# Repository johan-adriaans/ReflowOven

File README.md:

# ReflowOven
Arduino reflow oven voor de BEEA avond, 6 augustus 2015

De "bill-of-materials" staat [hier](board-v1/bill-of-materials.pdf).

## Opbouw reflow printje

Dit zijn de verbindingen op het bordje dat je gaat opbouwen:

### Stap 1: alle lage componenten

Let op de polariteit van de 3 LEDs en de zener diode!

Het knopje is een andere dan oorspronkelijk op de print voorzien is.

### Stap 2: drie connectoren

DC jack, kleine sensor aansluiting, grote heater aansluting:

Goed vastsolderen, vooral die DC voeding jack.

### Stap 3: Arduino Nano microcontroller

Pennen afknippen, zodat de onderkant redelijk vlak is.

### Stap 4: zoemer en extra dikke condensator

Let op polariteit van beide componenten:

### Stap 5: sensor + heater

De sensor in de groene schroefklemmen, heater in de blauwe:

Draden blank maken, liefst strippen en vertinnen, dan goed vastschroeven.

### Stap 6: software

Er moet een Arduino "sketch" in de Arduino worden geinstalleerd.  
Dat gaat via de USB stekker, en een USB driver voor de CH341 chip.  
De groene LED is altijd aan als de interne 5V regelaar stroom krijgt.

**Niet** de 19V voeding aansluiten tijdens deze actie!

### Stap 7

Controleren, controleren, controleren. En dan: _nog een laatste keertje..._  
Als bijvoorbeeld de zener verkeerd om zit, krijg je gegarandeerd vuurwerk.  
Pas als je zeker weet dat de zaak klopt, de 19V adapter inprikken.

Als alles goed aangesloten en ingesteld is, begint het plaatje warm te worden.  
Zet de zaak **alleen** aan als de heater goed in het koelblok geklemd zit!

## Opbouw demo bordje

...

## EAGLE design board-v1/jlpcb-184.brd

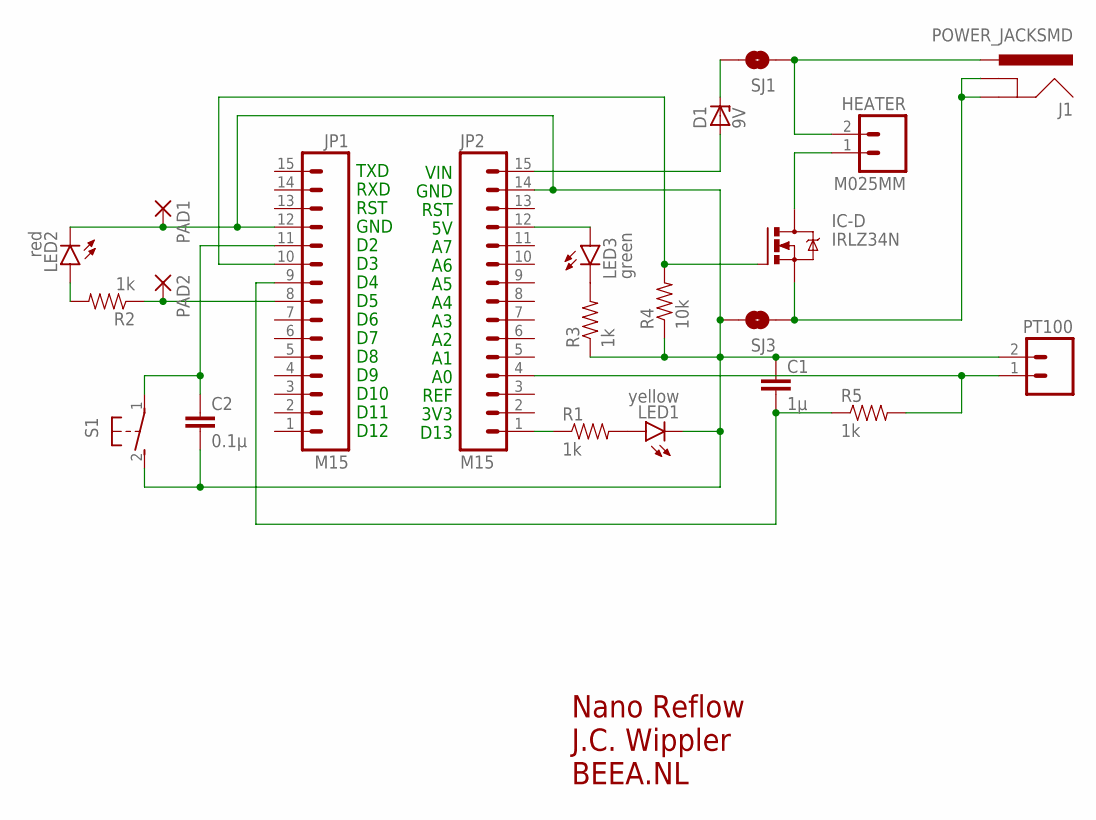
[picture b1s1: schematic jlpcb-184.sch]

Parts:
C1: 1µ; CAP-PTH-5MM
C2: 0.1µ; CAP-PTH-SMALL
D1: 9V; DO35Z10
HEATER: M025MM; SCREWTERMINAL-5MM-2
IC-D: IRLZ34N; TO220BV
J1: POWER_JACKSMD; POWER_JACK_SMD
JP1, JP2: M15; 1X15
LED1: yellow; LED3MM
LED2: red; LED3MM
LED3: green; LED3MM
PAD1, PAD2: 1,6/0,8
PT100: M023.5MM; SCREWTERMINAL-3.5MM-2
R1, R2, R3, R5: 1k; AXIAL-0.3
R4: 10k; AXIAL-0.3
S1: 31-XX; B3F-31XX
SJ1, SJ3: SOLDERJUMPERTRACE; SJ_2S-TRACE

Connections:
unnamed: D1.A, JP2.15
unnamed: D1.C, SJ1.2
unnamed: HEATER.1, IC-D.D
unnamed: IC-D.S, J1.GND (GNDBREAK), J1.P$4 (GND), SJ3.1
unnamed: C1.1, C2.2, JP1.12, JP2.14, LED1.K (C), LED2.K (C), PAD1.1, PT100.2, R3.P$1 (1), R4.P$1 (1), S1.2 (S), SJ3.2
unnamed: HEATER.2, J1.VIN0 (PWR), SJ1.1
unnamed: LED2.A, R2.P$2 (2)
unnamed: LED1.A, R1.P$2 (2)
unnamed: JP2.1, R1.P$1 (1)
unnamed: JP2.4, PT100.1, R5.P$2 (2)
unnamed: LED3.K (C), R3.P$2 (2)
unnamed: JP2.12, LED3.A
unnamed: IC-D.G, JP1.10, R4.P$2 (2)
unnamed: JP1.8, PAD2.1, R2.P$1 (1)
unnamed: C1.2, JP1.9, R5.P$1 (1)
unnamed: C2.1, JP1.11, S1.1

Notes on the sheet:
D12
D11
D10
GND
RST
RXD
TXD
D13
3V3
REF
VIN
Nano Reflow J.C. Wippler BEEA.NL

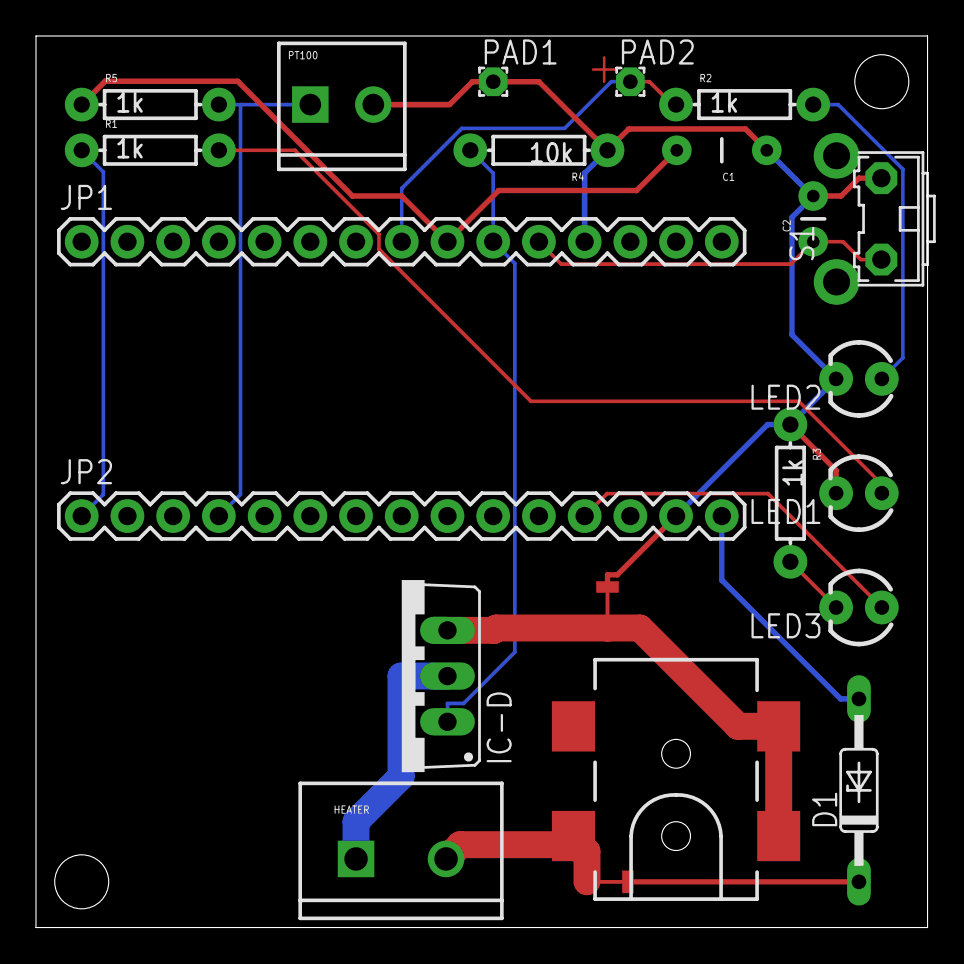
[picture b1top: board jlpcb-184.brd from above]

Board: 2 copper layers, 49.5 x 49.5 mm, 22 parts (0 on the bottom side), 16 nets.

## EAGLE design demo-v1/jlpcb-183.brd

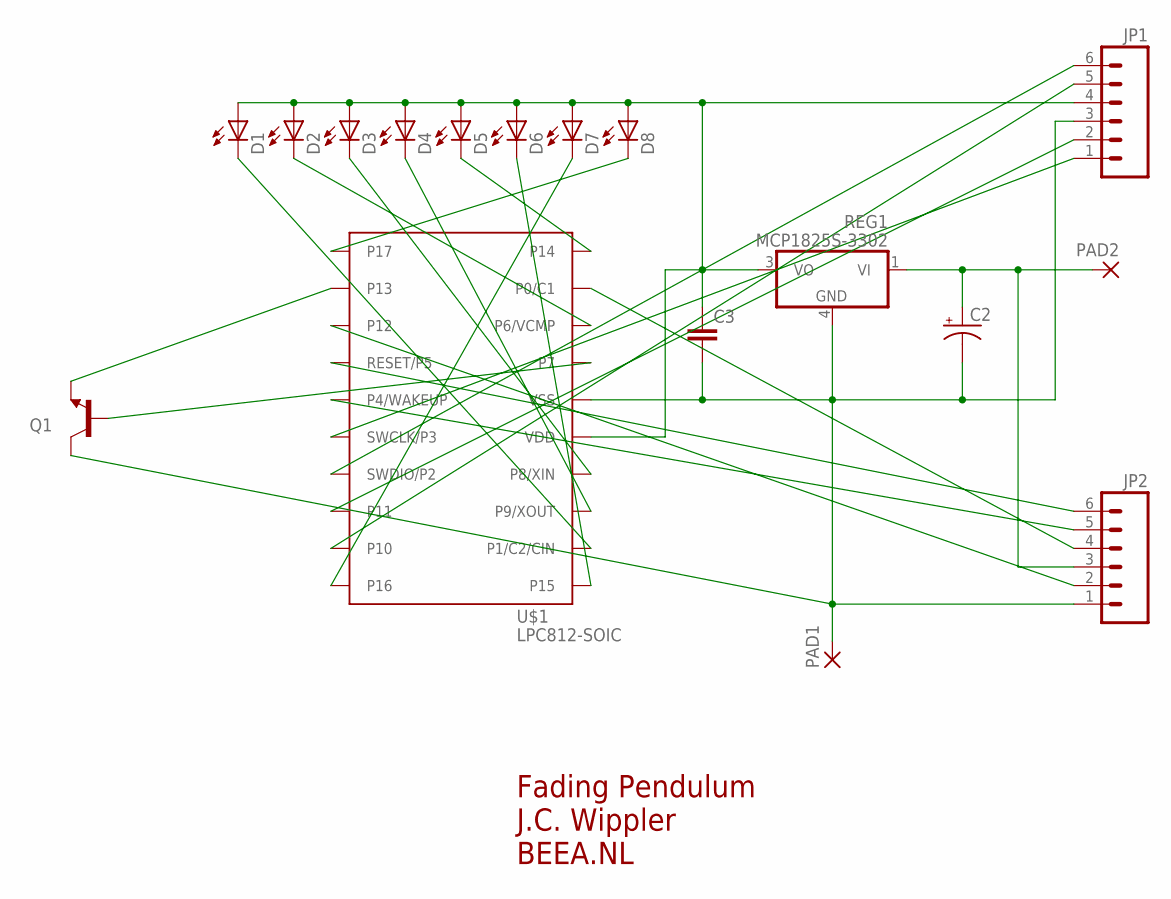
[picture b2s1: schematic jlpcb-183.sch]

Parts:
C2: CAP_POL1206; EIA3216
C3: CAP0805; 0805
D1, D2, D3, D4, D5, D6, D7, D8: LEDCHIP-LED0805; CHIP-LED0805
JP1, JP2: M06NO_SILK_FEMALE_PTH; 1X06_NO_SILK
PAD1, PAD2: SMD2; SMD1,27-2,54
Q1: TRANSISTOR_NPNSOT23-3; SOT23-3
REG1: MCP1825S-3302; SOT223
U$1: LPC812-SOIC; SOIC20

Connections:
unnamed: D1.C, U$1.12 (P1/C2/CIN)
unnamed: D2.C, U$1.18 (P6/VCMP)
unnamed: D3.C, U$1.14 (P8/XIN)
unnamed: D4.C, U$1.13 (P9/XOUT)
unnamed: D5.C, U$1.20 (P14)
unnamed: D6.C, U$1.11 (P15)
unnamed: D7.C, U$1.10 (P16)
unnamed: D8.C, U$1.1 (P17)
unnamed: C3.1, D1.A, D2.A, D3.A, D4.A, D5.A, D6.A, D7.A, D8.A, JP1.4, REG1.3 (VO), U$1.15 (VDD)
unnamed: C2.C (-), C3.2, JP1.3, JP2.1, PAD1.1, Q1.3 (C), REG1.4 (GND), U$1.16 (VSS)
unnamed: C2.A (+), JP2.3, PAD2.1, REG1.1 (VI)
unnamed: JP2.2, U$1.3 (P12)
unnamed: JP2.6, U$1.4 (RESET/P5)
unnamed: JP2.5, U$1.5 (P4/WAKEUP)
unnamed: JP2.4, U$1.19 (P0/C1)
unnamed: JP1.5, U$1.9 (P10)
unnamed: JP1.2, U$1.8 (P11)
unnamed: JP1.6, U$1.7 (SWDIO/P2)
unnamed: JP1.1, U$1.6 (SWCLK/P3)
unnamed: Q1.2 (E), U$1.2 (P13)
unnamed: Q1.1 (B), U$1.17 (P7)

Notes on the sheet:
Fading Pendulum J.C. Wippler BEEA.NL

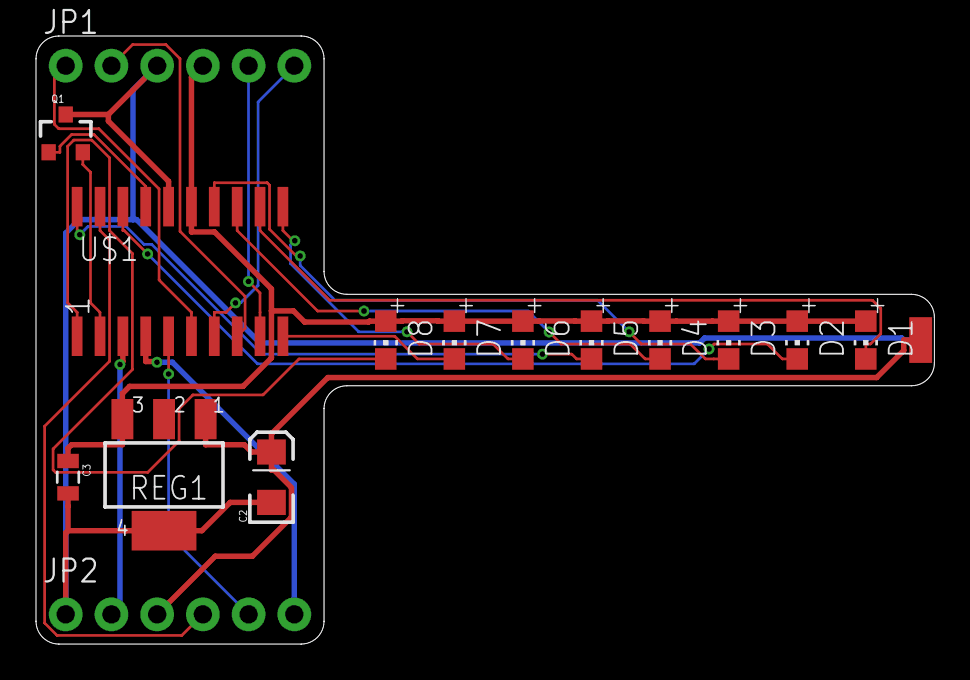
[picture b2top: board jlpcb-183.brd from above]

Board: 2 copper layers, 49.9 x 33.8 mm, 17 parts (1 on the bottom side), 21 nets.

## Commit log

2015-07-26 Initial import
2015-07-26 Heater now advertises power level through PWM on pin13. Changed heat profile
2015-07-26 Heater level led did nog have a PWM port :)
2015-07-26 Beeper was permanent ):
2015-07-26 Added heat profiles (as comments)
2015-07-26 Code cleanup
2015-08-06 add boards and photos
2015-08-06 build instructions (in Dutch)
2015-08-06 typo
2015-08-06 add BOM
2015-08-06 add link to BOM
2015-08-06 tweak

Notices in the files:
parts and their libraries:
SparkFun-Connectors: Licensing: Creative Commons ShareAlike 4.0 International - https://creativecommons.org/licenses/by-sa/4.0
